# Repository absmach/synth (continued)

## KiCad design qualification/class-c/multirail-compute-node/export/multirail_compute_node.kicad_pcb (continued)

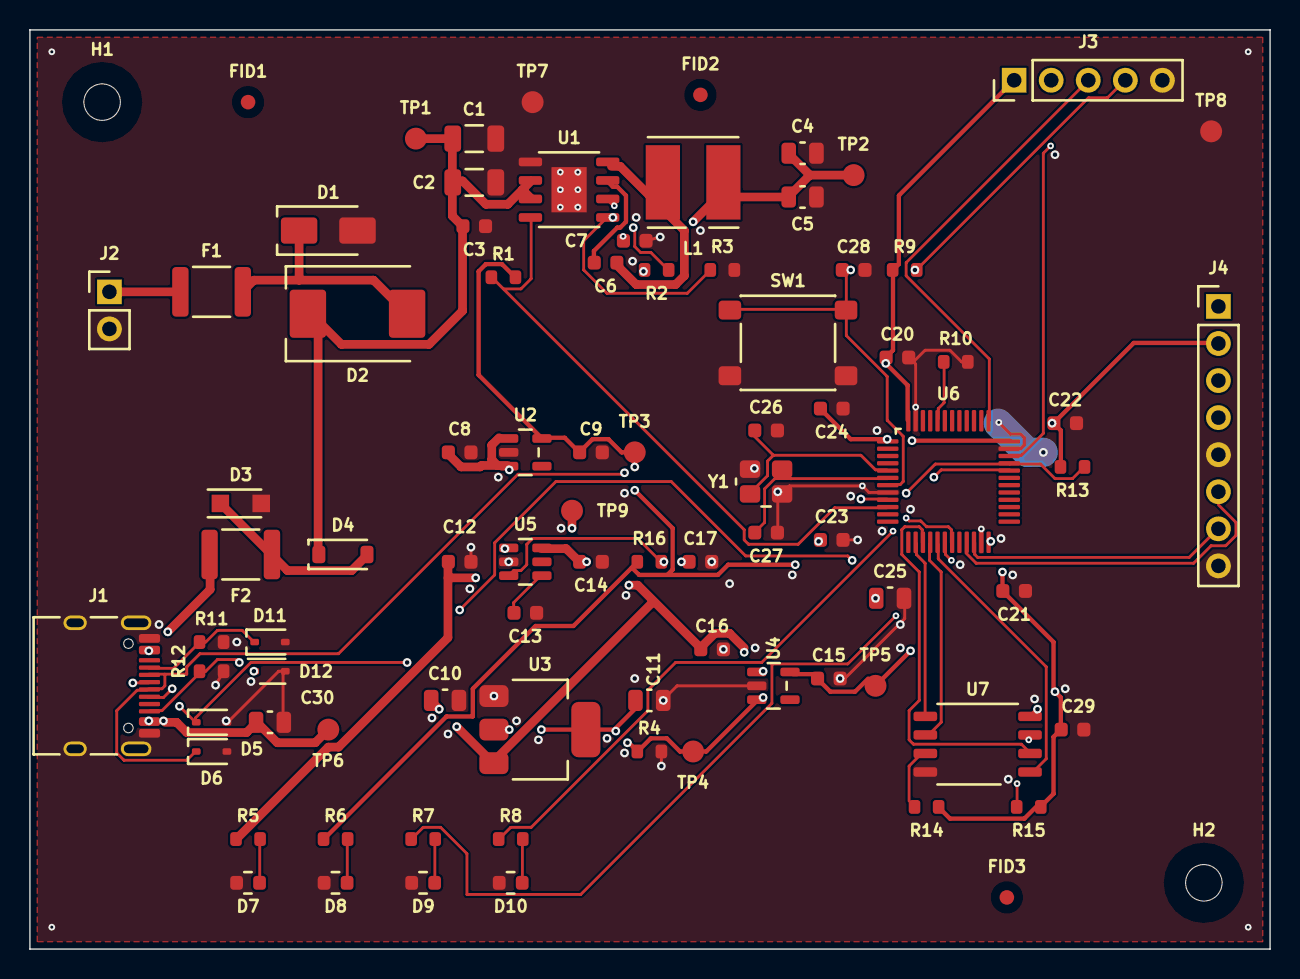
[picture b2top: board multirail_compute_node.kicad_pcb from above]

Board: 4 copper layers, 85.0 x 63.0 mm, 86 parts (0 on the bottom side), 42 nets.

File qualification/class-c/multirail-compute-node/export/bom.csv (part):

refdes,value,kind,description,kicad_symbol,kicad_footprint,lcsc_pn,mpn
C1,10uF,capacitor,"Generic 1206 ceramic capacitor, any value",Device:C,Capacitor_SMD:C_1206_3216Metric,,
C10,10uF,capacitor,"Generic 0805 MLCC, X7R/X5R, any value",Device:C,Capacitor_SMD:C_0805_2012Metric,,
C11,10uF,capacitor,"Generic 0805 MLCC, X7R/X5R, any value",Device:C,Capacitor_SMD:C_0805_2012Metric,,
C12,1uF,capacitor,"Generic 0603 MLCC, X7R/X5R, any value",Device:C,Capacitor_SMD:C_0603_1608Metric,,
C13,1nF,capacitor,"Generic 0603 MLCC, X7R/X5R, any value",Device:C,Capacitor_SMD:C_0603_1608Metric,,
C14,1uF,capacitor,"Generic 0603 MLCC, X7R/X5R, any value",Device:C,Capacitor_SMD:C_0603_1608Metric,,
C15,1uF,capacitor,"Generic 0603 MLCC, X7R/X5R, any value",Device:C,Capacitor_SMD:C_0603_1608Metric,,
C16,1uF,capacitor,"Generic 0603 MLCC, X7R/X5R, any value",Device:C,Capacitor_SMD:C_0603_1608Metric,,
C17,100nF,capacitor,"Generic 0603 MLCC, X7R/X5R, any value",Device:C,Capacitor_SMD:C_0603_1608Metric,,
C2,10uF,capacitor,"Generic 1206 ceramic capacitor, any value",Device:C,Capacitor_SMD:C_1206_3216Metric,,
C20,100nF,capacitor,"Generic 0603 MLCC, X7R/X5R, any value",Device:C,Capacitor_SMD:C_0603_1608Metric,,
C21,100nF,capacitor,"Generic 0603 MLCC, X7R/X5R, any value",Device:C,Capacitor_SMD:C_0603_1608Metric,,
C22,100nF,capacitor,"Generic 0603 MLCC, X7R/X5R, any value",Device:C,Capacitor_SMD:C_0603_1608Metric,,
C23,100nF,capacitor,"Generic 0603 MLCC, X7R/X5R, any value",Device:C,Capacitor_SMD:C_0603_1608Metric,,
C24,100nF,capacitor,"Generic 0603 MLCC, X7R/X5R, any value",Device:C,Capacitor_SMD:C_0603_1608Metric,,
C25,4.7uF,capacitor,"Generic 0805 MLCC, X7R/X5R, any value",Device:C,Capacitor_SMD:C_0805_2012Metric,,
C26,10pF,capacitor,"Generic 0603 MLCC, X7R/X5R, any value",Device:C,Capacitor_SMD:C_0603_1608Metric,,
C27,10pF,capacitor,"Generic 0603 MLCC, X7R/X5R, any value",Device:C,Capacitor_SMD:C_0603_1608Metric,,
C28,100nF,capacitor,"Generic 0603 MLCC, X7R/X5R, any value",Device:C,Capacitor_SMD:C_0603_1608Metric,,
C29,100nF,capacitor,"Generic 0603 MLCC, X7R/X5R, any value",Device:C,Capacitor_SMD:C_0603_1608Metric,,
C3,220nF,capacitor,"Generic 0603 MLCC, X7R/X5R, any value",Device:C,Capacitor_SMD:C_0603_1608Metric,,
C30,10uF,capacitor,"Generic 0805 MLCC, X7R/X5R, any value",Device:C,Capacitor_SMD:C_0805_2012Metric,,
C4,22uF,capacitor,"Generic 0805 MLCC, X7R/X5R, any value",Device:C,Capacitor_SMD:C_0805_2012Metric,,
C5,22uF,capacitor,"Generic 0805 MLCC, X7R/X5R, any value",Device:C,Capacitor_SMD:C_0805_2012Metric,,
C6,100nF,capacitor,"Generic 0603 MLCC, X7R/X5R, any value",Device:C,Capacitor_SMD:C_0603_1608Metric,,
C7,1uF,capacitor,"Generic 0603 MLCC, X7R/X5R, any value",Device:C,Capacitor_SMD:C_0603_1608Metric,,
C8,1uF,capacitor,"Generic 0603 MLCC, X7R/X5R, any value",Device:C,Capacitor_SMD:C_0603_1608Metric,,
C9,1uF,capacitor,"Generic 0603 MLCC, X7R/X5R, any value",Device:C,Capacitor_SMD:C_0603_1608Metric,,
D1,SMAJ15A,diode,"Littelfuse SMAJ15A 400 W unidirectional TVS, 15 V standoff, 24.4 V clamp, DO-214AC, for a 12 V input",Device:D_Zener,Diode_SMD:D_SMA,,SMAJ15A
D10,(no value),diode,"Amber surface-mount LED, 0603",Device:LED,LED_SMD:LED_0603_1608Metric,,
D11,(no value),diode,"5V unidirectional TVS diode, SOD-123 — ESD protection",Device:D_TVS,Diode_SMD:D_SOD-323,,
D12,(no value),diode,"5V unidirectional TVS diode, SOD-123 — ESD protection",Device:D_TVS,Diode_SMD:D_SOD-323,,
D2,SS36,diode,"Vishay SS36 60 V 3 A Schottky rectifier, SMC (DO-214AB), for reverse-polarity blocking",Device:D_Schottky,Diode_SMD:D_SMC,,SS36
D3,PTVS6V0S1UR,diode,"Nexperia PTVS6V0S1UR 400 W unidirectional TVS, 6.0 V standoff, SOD123W, for VBUS and CC",Device:D_Zener,Diode_SMD:Nexperia_CFP3_SOD-123W,,PTVS6V0S1UR
D4,1N5819HW-7-F,diode,"Diodes Inc. 1N5819HW-7-F, 40 V 1 A Schottky diode, SOD-123, low forward voltage",Device:D_Schottky,Diode_SMD:D_SOD-123,C82544,1N5819HW-7-F
D5,(no value),diode,"USB-line ESD protection (TVS diode array), bidirectional",Device:D_TVS,Diode_SMD:D_SOD-323,,
D6,(no value),diode,"USB-line ESD protection (TVS diode array), bidirectional",Device:D_TVS,Diode_SMD:D_SOD-323,,
D7,0603-RED,diode,"Red LED, 0603 package, ~2.0V Vf",Device:LED,LED_SMD:LED_0603_1608Metric,C2286,0603-RED
D8,0603-GREEN,diode,"Green LED, 0603 package, ~2.2V Vf",Device:LED,LED_SMD:LED_0603_1608Metric,C72043,0603-GREEN
D9,(no value),diode,"Amber surface-mount LED, 0603",Device:LED,LED_SMD:LED_0603_1608Metric,,
F1,MF-MSMF110/16-2,fuse,"Bourns MF-MSMF110/16-2 resettable fuse, 1.1 A hold, 16 V, 1812",Device:Polyfuse,Fuse:Fuse_1812_4532Metric,C210834,MF-MSMF110/16-2
F2,MF-MSMF110/16-2,fuse,"Bourns MF-MSMF110/16-2 resettable fuse, 1.1 A hold, 16 V, 1812",Device:Polyfuse,Fuse:Fuse_1812_4532Metric,C210834,MF-MSMF110/16-2
FID1,(no value),fiducial,1 mm fiducial mark for pick-and-place alignment,Mechanical:Fiducial,Fiducial:Fiducial_1mm_Mask2mm,,
FID2,(no value),fiducial,1 mm fiducial mark for pick-and-place alignment,Mechanical:Fiducial,Fiducial:Fiducial_1mm_Mask2mm,,
FID3,(no value),fiducial,1 mm fiducial mark for pick-and-place alignment,Mechanical:Fiducial,Fiducial:Fiducial_1mm_Mask2mm,,
H1,(no value),mounting_hole,M2.5 non-plated mounting hole (NPTH) for a board corner,Mechanical:MountingHole,MountingHole:MountingHole_2.5mm,,
H2,(no value),mounting_hole,M2.5 non-plated mounting hole (NPTH) for a board corner,Mechanical:MountingHole,MountingHole:MountingHole_2.5mm,,
J1,TYPE-C-31-M-12,connector,"USB-C receptacle, 24-pin SMD. Modelled here with primary and mirrored power/ground/data pins for full pad coverage.",Connector:USB_C_Receptacle,Connector_USB:USB_C_Receptacle_HRO_TYPE-C-31-M-12,C165948,TYPE-C-31-M-12
J2,HX PZ2.54-1x2P ZZ,connector,"1x2 through-hole pin header, 2.54mm pitch, for a jumper",Connector_Generic:Conn_01x02,Connector_PinHeader_2.54mm:PinHeader_1x02_P2.54mm_Vertical,C32713268,HX PZ2.54-1x2P ZZ
J3,(no value),connector,"1x5 through-hole pin header, 2.54 mm pitch, vertical, for the SWD port. No current rating asserted.",Connector_Generic:Conn_01x05,Connector_PinHeader_2.54mm:PinHeader_1x05_P2.54mm_Vertical,,
J4,M20-9990846,connector,"Harwin M20-9990846 1x8 through-hole pin header, 2.54 mm pitch, vertical, 3 A per contact",Connector_Generic:Conn_01x08,Connector_PinHeader_2.54mm:PinHeader_1x08_P2.54mm_Vertical,,M20-9990846
L1,SRN6045TA-6R8M,inductor,"Bourns SRN6045TA-6R8M 6.8 uH semi-shielded power inductor, 6.0 x 6.0 mm. Datasheet typ: Isat 5.7 A (L drops 30%), Irms 3.6 A (max_current_ma is Irms), DCR 34 mOhm +-20%",Device:L,Inductor_SMD:L_Bourns_SRN6045TA,,SRN6045TA-6R8M
R1,10k,resistor,"Generic 0603 thick-film resistor, any value",Device:R_US,Resistor_SMD:R_0603_1608Metric,,
R10,10k,resistor,"Generic 0603 thick-film resistor, any value",Device:R_US,Resistor_SMD:R_0603_1608Metric,,
R11,5.1k,resistor,"Generic 0603 thick-film resistor, any value",Device:R_US,Resistor_SMD:R_0603_1608Metric,,
R12,5.1k,resistor,"Generic 0603 thick-film resistor, any value",Device:R_US,Resistor_SMD:R_0603_1608Metric,,
R13,1.5k,resistor,"Generic 0603 thick-film resistor, any value",Device:R_US,Resistor_SMD:R_0603_1608Metric,,
R14,10k,resistor,"Generic 0603 thick-film resistor, any value",Device:R_US,Resistor_SMD:R_0603_1608Metric,,
R15,10k,resistor,"Generic 0603 thick-film resistor, any value",Device:R_US,Resistor_SMD:R_0603_1608Metric,,
R16,100k,resistor,"Generic 0603 thick-film resistor, any value",Device:R_US,Resistor_SMD:R_0603_1608Metric,,
R2,10k,resistor,"Generic 0603 thick-film resistor, any value",Device:R_US,Resistor_SMD:R_0603_1608Metric,,
R3,3.83k,resistor,"Generic 0603 thick-film resistor, any value",Device:R_US,Resistor_SMD:R_0603_1608Metric,,
R4,330,resistor,"Generic 0603 thick-film resistor, any value",Device:R_US,Resistor_SMD:R_0603_1608Metric,,
R5,680,resistor,"Generic 0603 thick-film resistor, any value",Device:R_US,Resistor_SMD:R_0603_1608Metric,,
R6,470,resistor,"Generic 0603 thick-film resistor, any value",Device:R_US,Resistor_SMD:R_0603_1608Metric,,
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
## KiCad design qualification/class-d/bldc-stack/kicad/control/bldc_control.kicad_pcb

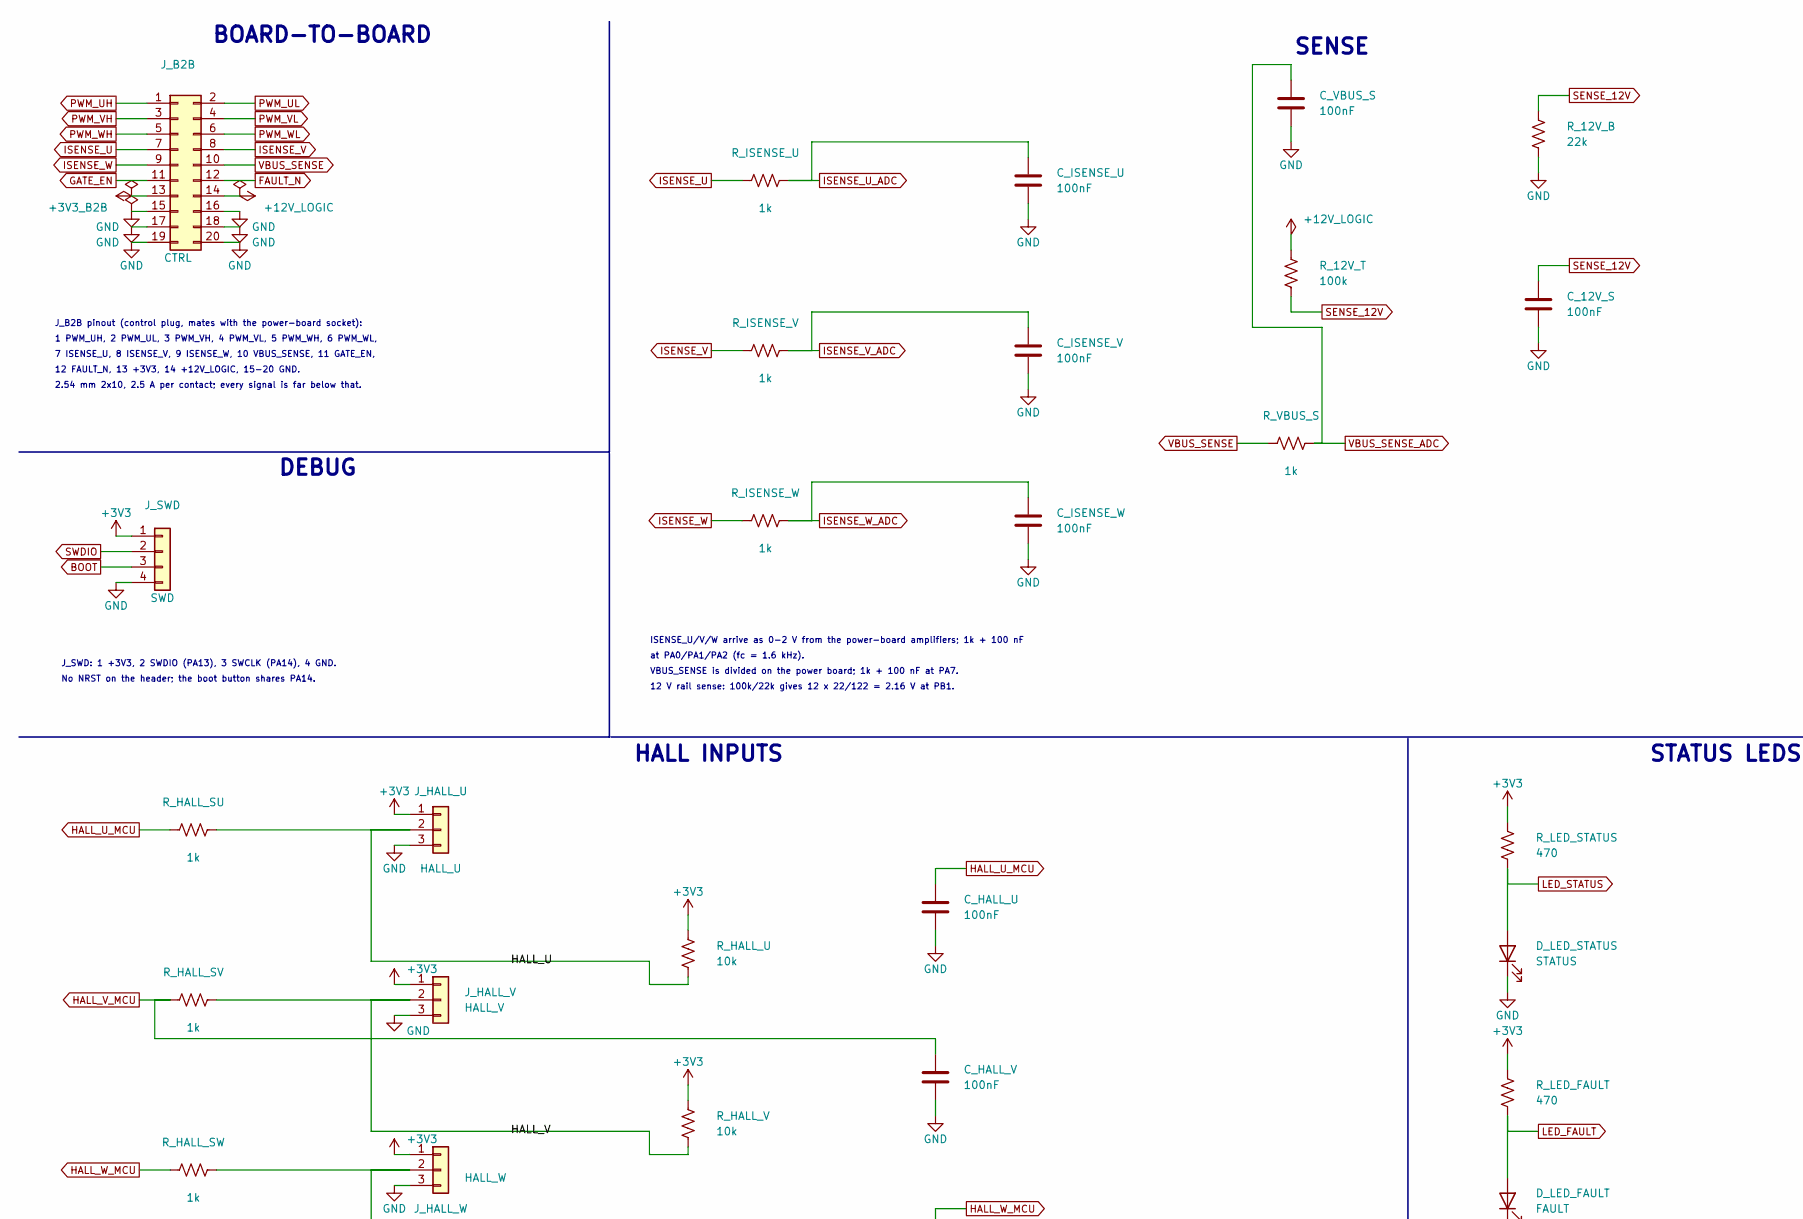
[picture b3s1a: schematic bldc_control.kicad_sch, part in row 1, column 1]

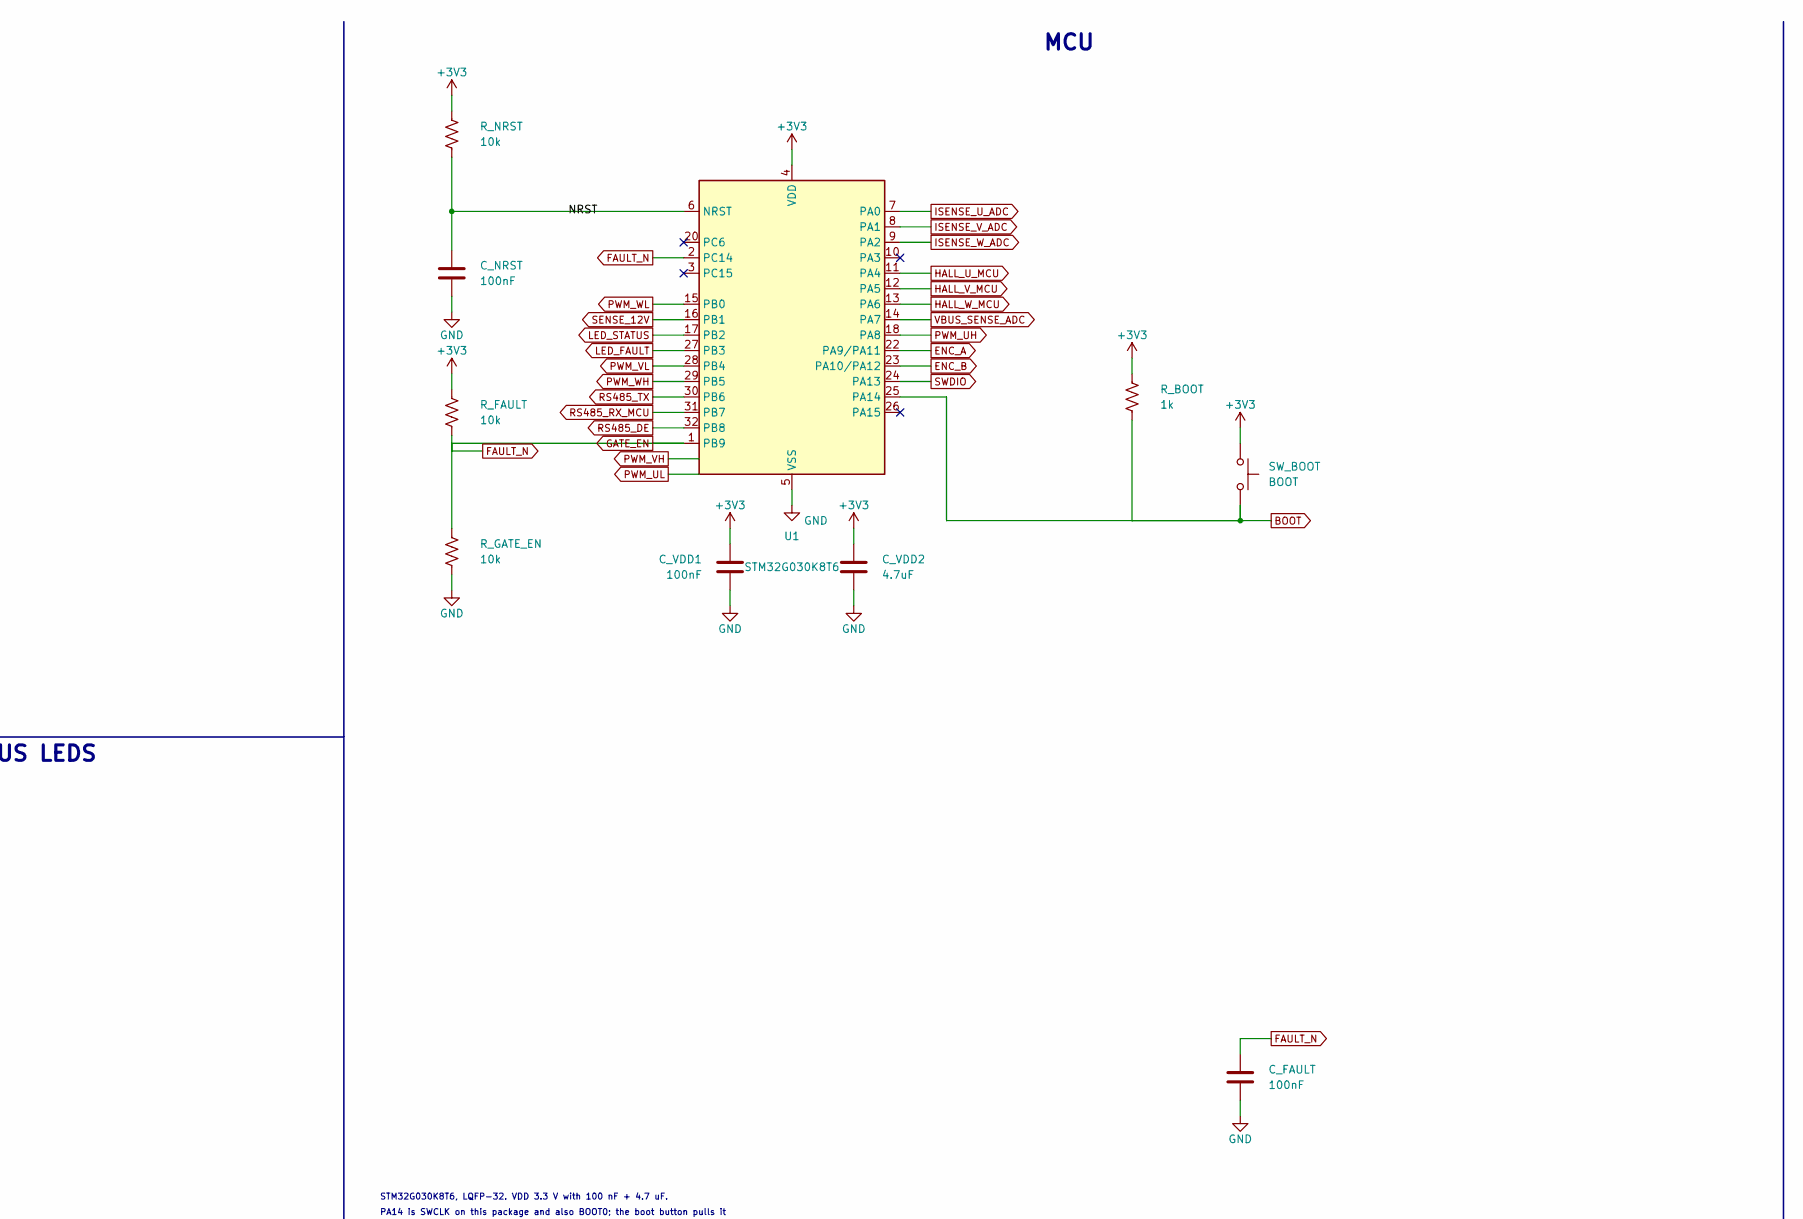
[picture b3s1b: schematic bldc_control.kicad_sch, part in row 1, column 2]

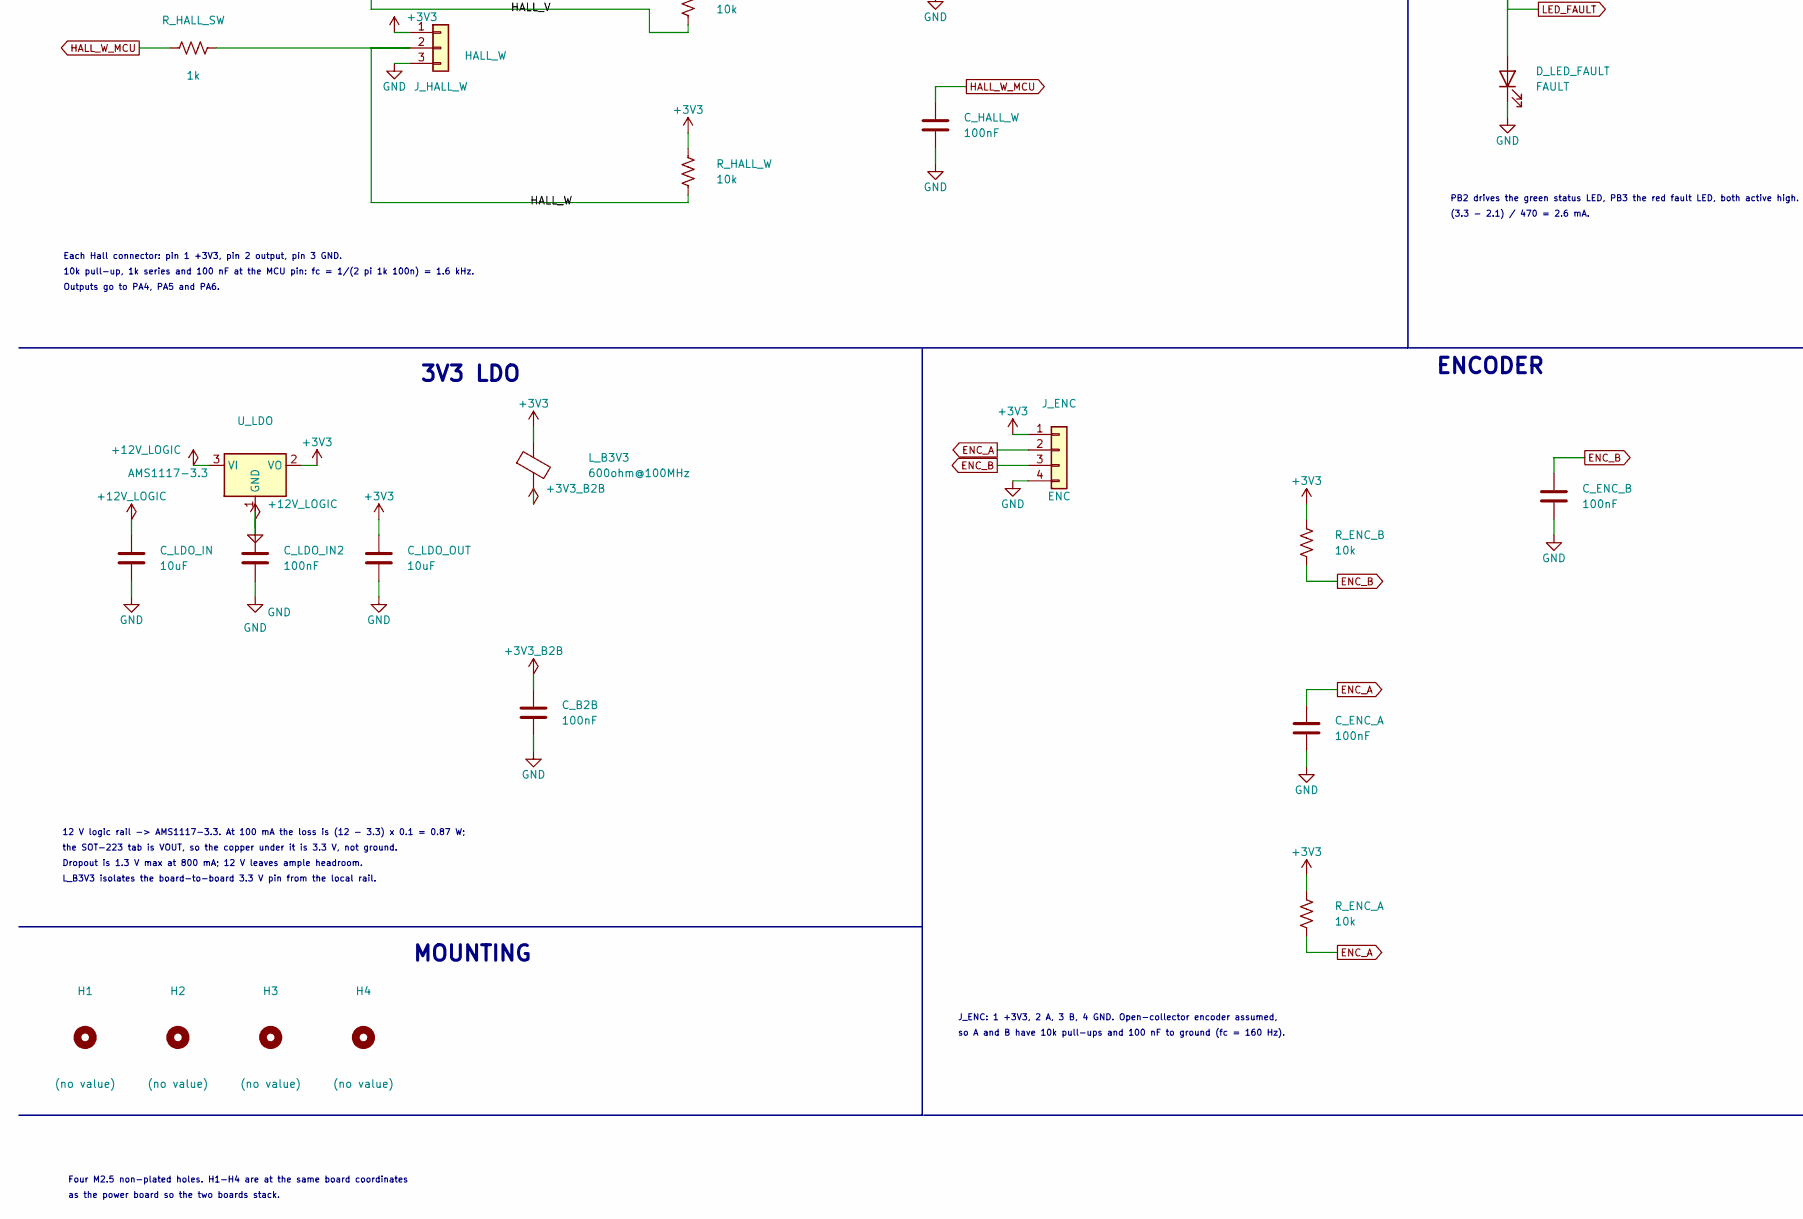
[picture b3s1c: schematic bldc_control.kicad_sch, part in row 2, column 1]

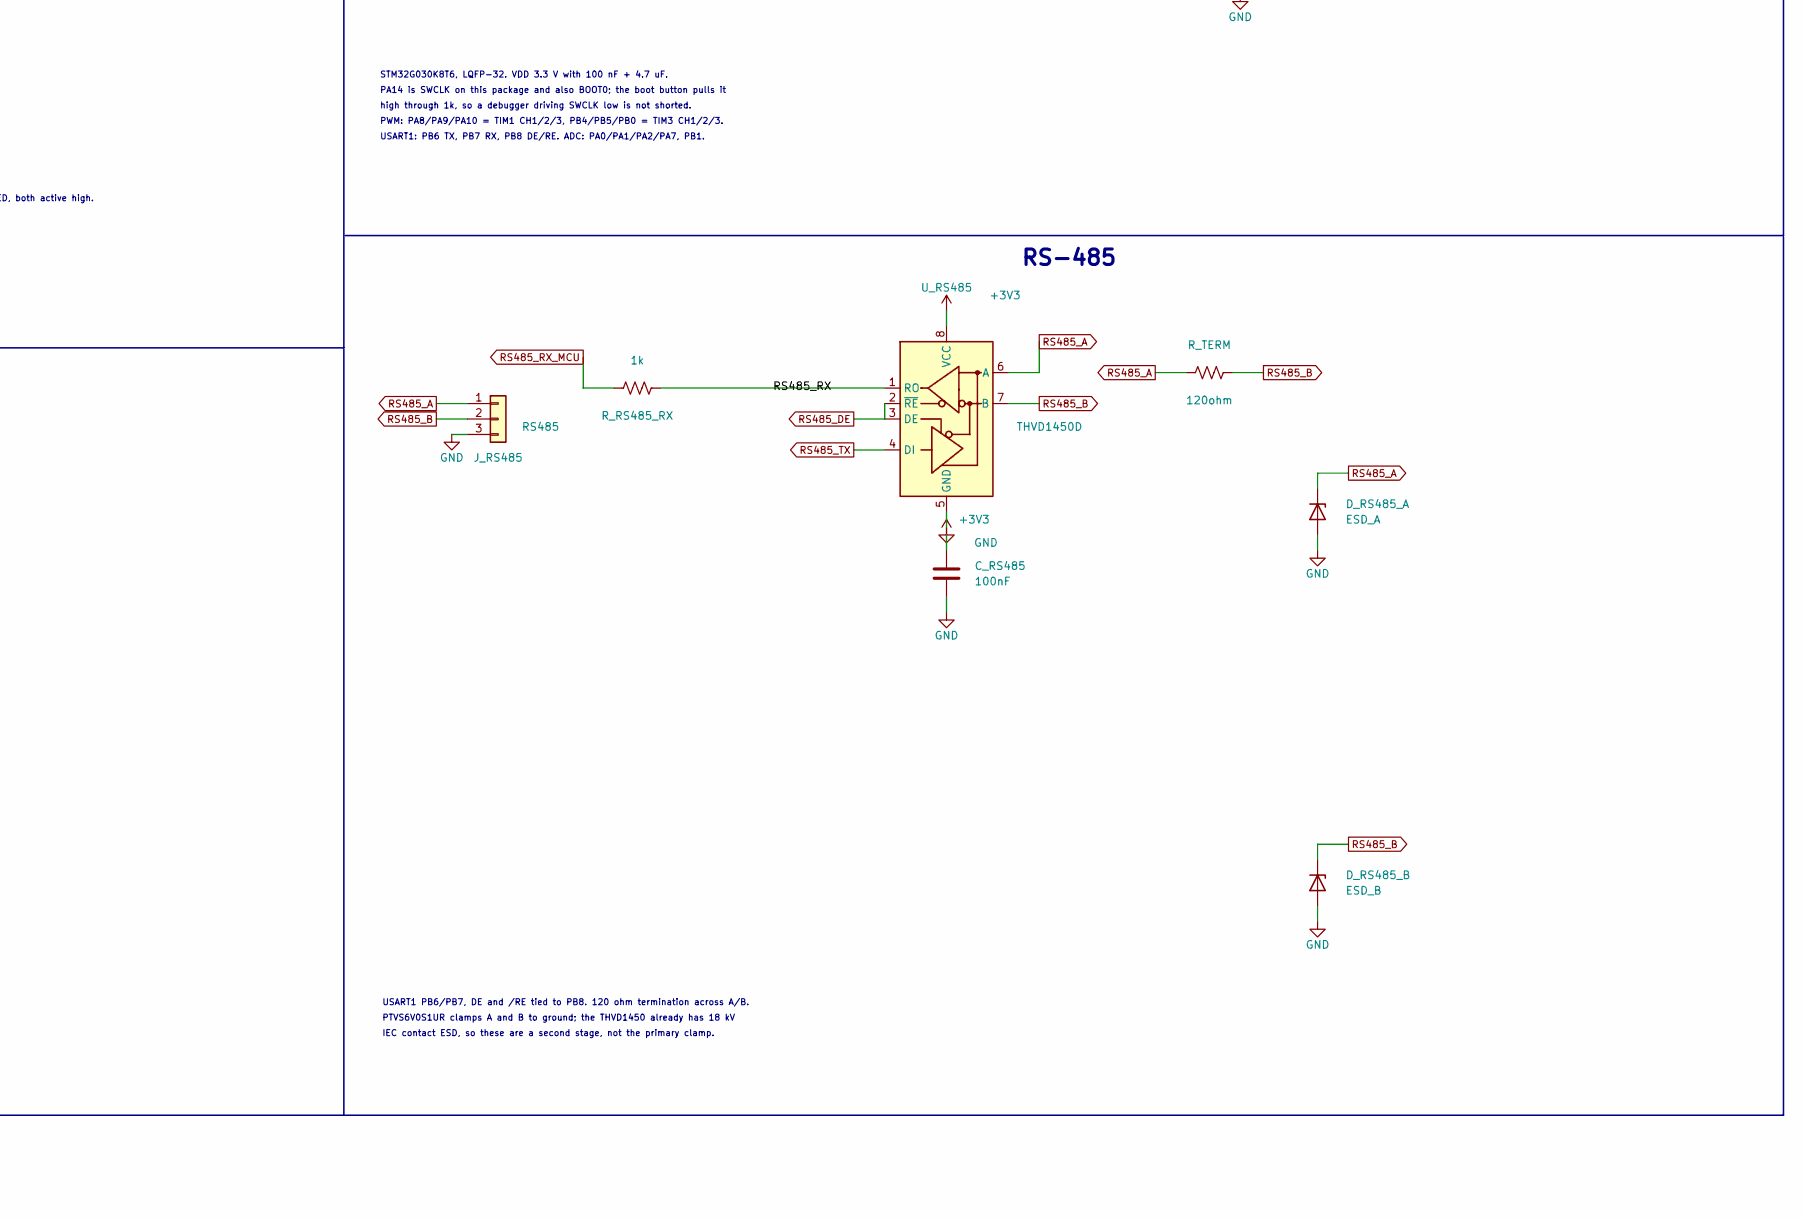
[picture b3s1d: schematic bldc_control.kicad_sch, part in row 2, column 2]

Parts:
C_12V_S: 100nF; C_0603_1608Metric; Voltage 16V
C_B2B: 100nF; C_0603_1608Metric; Voltage 16V
C_ENC_A: 100nF; C_0603_1608Metric; Voltage 16V
C_ENC_B: 100nF; C_0603_1608Metric; Voltage 16V
C_FAULT: 100nF; C_0603_1608Metric; Voltage 16V
C_HALL_U: 100nF; C_0603_1608Metric; Voltage 16V
C_HALL_V: 100nF; C_0603_1608Metric; Voltage 16V
C_HALL_W: 100nF; C_0603_1608Metric; Voltage 16V
C_ISENSE_U: 100nF; C_0603_1608Metric; Voltage 16V
C_ISENSE_V: 100nF; C_0603_1608Metric; Voltage 16V
C_ISENSE_W: 100nF; C_0603_1608Metric; Voltage 16V
C_LDO_IN: 10uF; C_1206_3216Metric; Voltage 50V
C_LDO_IN2: 100nF; C_0603_1608Metric; Voltage 50V
C_LDO_OUT: 10uF; C_0603_1608Metric; Voltage 16V
C_NRST: 100nF; C_0603_1608Metric; Voltage 16V
C_RS485: 100nF; C_0603_1608Metric; Voltage 16V
C_VBUS_S: 100nF; C_0603_1608Metric; Voltage 16V
C_VDD1: 100nF; C_0603_1608Metric; Voltage 16V
C_VDD2: 4.7uF; C_0603_1608Metric; Voltage 16V
D_LED_FAULT: FAULT; LED_0603_1608Metric; MPN LTST-C190KRKT
D_LED_STATUS: STATUS; LED_0603_1608Metric; MPN LTST-C190KGKT
D_RS485_A: ESD_A; Nexperia_CFP3_SOD-123W; MPN PTVS6V0S1UR
D_RS485_B: ESD_B; Nexperia_CFP3_SOD-123W; MPN PTVS6V0S1UR
H1, H2, H3, H4: (no value); MountingHole_2.5mm
J_B2B: CTRL; PinHeader_2x10_P2.54mm_Vertical; MPN 2.54-2*10; LCSC C5116480
J_ENC: ENC; PinHeader_1x04_P2.54mm_Vertical; MPN PZ254V-11-04P; LCSC C492403
J_HALL_U: HALL_U; PinHeader_1x03_P2.54mm_Vertical
J_HALL_V: HALL_V; PinHeader_1x03_P2.54mm_Vertical
J_HALL_W: HALL_W; PinHeader_1x03_P2.54mm_Vertical
J_RS485: RS485; PinHeader_1x03_P2.54mm_Vertical
J_SWD: SWD; PinHeader_1x04_P2.54mm_Vertical; MPN PZ254V-11-04P; LCSC C492403
L_B3V3: 600ohm@100MHz; L_0603_1608Metric
R_12V_B: 22k; R_0603_1608Metric; Tolerance 1%
R_12V_T: 100k; R_0603_1608Metric; Tolerance 1%
R_BOOT: 1k; R_0603_1608Metric
R_ENC_A: 10k; R_0603_1608Metric
R_ENC_B: 10k; R_0603_1608Metric
R_FAULT: 10k; R_0603_1608Metric
R_GATE_EN: 10k; R_0603_1608Metric
R_HALL_SU: 1k; R_0603_1608Metric
R_HALL_SV: 1k; R_0603_1608Metric
R_HALL_SW: 1k; R_0603_1608Metric
R_HALL_U: 10k; R_0603_1608Metric
R_HALL_V: 10k; R_0603_1608Metric
R_HALL_W: 10k; R_0603_1608Metric
R_ISENSE_U: 1k; R_0603_1608Metric
R_ISENSE_V: 1k; R_0603_1608Metric
R_ISENSE_W: 1k; R_0603_1608Metric
R_LED_FAULT: 470; R_0603_1608Metric
R_LED_STATUS: 470; R_0603_1608Metric
R_NRST: 10k; R_0603_1608Metric
R_RS485_RX: 1k; R_0603_1608Metric
R_TERM: 120ohm; R_0603_1608Metric; Tolerance 1%
R_VBUS_S: 1k; R_0603_1608Metric
SW_BOOT: BOOT; SW_SPST_PTS645Sx43SMTR92; MPN PTS645SM43SMTR92 LFS; LCSC C221880
U1: STM32G030K8T6; LQFP-32_7x7mm_P0.8mm
U_LDO: AMS1117-3.3; SOT-223-3_TabPin2; MPN AMS1117-3.3; LCSC C6186
U_RS485: THVD1450D; SOIC-8_3.9x4.9mm_P1.27mm; MPN THVD1450D; LCSC C2671361

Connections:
+3V3: C_LDO_OUT.1, C_RS485.1, C_VDD1.1, C_VDD2.1, J_ENC.1, J_HALL_U.1, J_HALL_V.1, J_HALL_W.1, J_SWD.1, L_B3V3.1, R_BOOT.1, R_ENC_A.2, R_ENC_B.2, R_FAULT.1, R_HALL_U.2, R_HALL_V.2, R_HALL_W.2, R_LED_FAULT.1, R_LED_STATUS.1, R_NRST.1, SW_BOOT.1, U1.4 (VDD), U_LDO.2 (VO), U_RS485.8 (VCC)
+3V3_B2B: C_B2B.1, J_B2B.13, L_B3V3.2
BOOT: J_SWD.3, R_BOOT.2, SW_BOOT.2, U1.25 (PA14)
ENC_A: C_ENC_A.1, J_ENC.2, R_ENC_A.1, U1.22 (PA9/PA11)
ENC_B: C_ENC_B.1, J_ENC.3, R_ENC_B.1, U1.23 (PA10/PA12)
FAULT_N: C_FAULT.1, J_B2B.12, R_FAULT.2, U1.2 (PC14)
GATE_EN: J_B2B.11, R_GATE_EN.1, U1.1 (PB9)
HALL_U: J_HALL_U.2, R_HALL_SU.1, R_HALL_U.1
HALL_U_MCU: C_HALL_U.1, R_HALL_SU.2, U1.11 (PA4)
HALL_V: J_HALL_V.2, R_HALL_SV.1, R_HALL_V.1
HALL_V_MCU: C_HALL_V.1, R_HALL_SV.2, U1.12 (PA5)
HALL_W: J_HALL_W.2, R_HALL_SW.1, R_HALL_W.1
HALL_W_MCU: C_HALL_W.1, R_HALL_SW.2, U1.13 (PA6)
ISENSE_U: J_B2B.7, R_ISENSE_U.1
ISENSE_U_ADC: C_ISENSE_U.1, R_ISENSE_U.2, U1.7 (PA0)
ISENSE_V: J_B2B.8, R_ISENSE_V.1
ISENSE_V_ADC: C_ISENSE_V.1, R_ISENSE_V.2, U1.8 (PA1)
ISENSE_W: J_B2B.9, R_ISENSE_W.1
ISENSE_W_ADC: C_ISENSE_W.1, R_ISENSE_W.2, U1.9 (PA2)
LED_FAULT: D_LED_FAULT.2 (A), R_LED_FAULT.2, U1.27 (PB3)
LED_STATUS: D_LED_STATUS.2 (A), R_LED_STATUS.2, U1.17 (PB2)
NRST: C_NRST.1, R_NRST.2, U1.6 (NRST)
PWM_UH: J_B2B.1, U1.18 (PA8)
PWM_UL: J_B2B.2, U1.19 (NC/PA9)
PWM_VH: J_B2B.3, U1.21 (NC/PA10)
PWM_VL: J_B2B.4, U1.28 (PB4)
PWM_WH: J_B2B.5, U1.29 (PB5)
PWM_WL: J_B2B.6, U1.15 (PB0)
RS485_A: D_RS485_A.1 (K), J_RS485.1, R_TERM.1, U_RS485.6 (A)
RS485_B: D_RS485_B.1 (K), J_RS485.2, R_TERM.2, U_RS485.7 (B)
RS485_DE: U1.32 (PB8), U_RS485.2 (~RE), U_RS485.3 (DE)
RS485_RX: R_RS485_RX.1, U_RS485.1 (RO)
RS485_RX_MCU: R_RS485_RX.2, U1.31 (PB7)
RS485_TX: U1.30 (PB6), U_RS485.4 (DI)
SENSE_12V: C_12V_S.1, R_12V_B.1, R_12V_T.2, U1.16 (PB1)
SWDIO: J_SWD.2, U1.24 (PA13)
VBUS_SENSE: J_B2B.10, R_VBUS_S.1
VBUS_SENSE_ADC: C_VBUS_S.1, R_VBUS_S.2, U1.14 (PA7)

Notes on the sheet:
MOUNTING
BOARD-TO-BOARD
3V3 LDO
MCU
HALL INPUTS
ENCODER
RS-485
DEBUG
STATUS LEDS
SENSE
J_B2B pinout (control plug, mates with the power-board socket):
1 PWM_UH, 2 PWM_UL, 3 PWM_VH, 4 PWM_VL, 5 PWM_WH, 6 PWM_WL,
7 ISENSE_U, 8 ISENSE_V, 9 ISENSE_W, 10 VBUS_SENSE, 11 GATE_EN,
12 FAULT_N, 13 +3V3, 14 +12V_LOGIC, 15-20 GND.
2.54 mm 2x10, 2.5 A per contact; every signal is far below that.
12 V logic rail -> AMS1117-3.3. At 100 mA the loss is (12 - 3.3) x 0.1 = 0.87 W;
the SOT-223 tab is VOUT, so the copper under it is 3.3 V, not ground.
Dropout is 1.3 V max at 800 mA; 12 V leaves ample headroom.
L_B3V3 isolates the board-to-board 3.3 V pin from the local rail.
STM32G030K8T6, LQFP-32. VDD 3.3 V with 100 nF + 4.7 uF.
PA14 is SWCLK on this package and also BOOT0; the boot button pulls it
high through 1k, so a debugger driving SWCLK low is not shorted.
PWM: PA8/PA9/PA10 = TIM1 CH1/2/3, PB4/PB5/PB0 = TIM3 CH1/2/3.
USART1: PB6 TX, PB7 RX, PB8 DE/RE. ADC: PA0/PA1/PA2/PA7, PB1.
Each Hall connector: pin 1 +3V3, pin 2 output, pin 3 GND.
10k pull-up, 1k series and 100 nF at the MCU pin: fc = 1/(2 pi 1k 100n) = 1.6 kHz.
Outputs go to PA4, PA5 and PA6.
J_ENC: 1 +3V3, 2 A, 3 B, 4 GND. Open-collector encoder assumed,
so A and B have 10k pull-ups and 100 nF to ground (fc = 160 Hz).
USART1 PB6/PB7, DE and /RE tied to PB8. 120 ohm termination across A/B.
PTVS6V0S1UR clamps A and B to ground; the THVD1450 already has 18 kV
IEC contact ESD, so these are a second stage, not the primary clamp.
J_SWD: 1 +3V3, 2 SWDIO (PA13), 3 SWCLK (PA14), 4 GND.
No NRST on the header; the boot button shares PA14.
PB2 drives the green status LED, PB3 the red fault LED, both active high.
(3.3 - 2.1) / 470 = 2.6 mA.
ISENSE_U/V/W arrive as 0-2 V from the power-board amplifiers; 1k + 100 nF
at PA0/PA1/PA2 (fc = 1.6 kHz).
VBUS_SENSE is divided on the power board; 1k + 100 nF at PA7.
12 V rail sense: 100k/22k gives 12 x 22/122 = 2.16 V at PB1.

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
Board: 6 copper layers, 61 parts (0 on the bottom side), 40 nets, no tracks yet.
